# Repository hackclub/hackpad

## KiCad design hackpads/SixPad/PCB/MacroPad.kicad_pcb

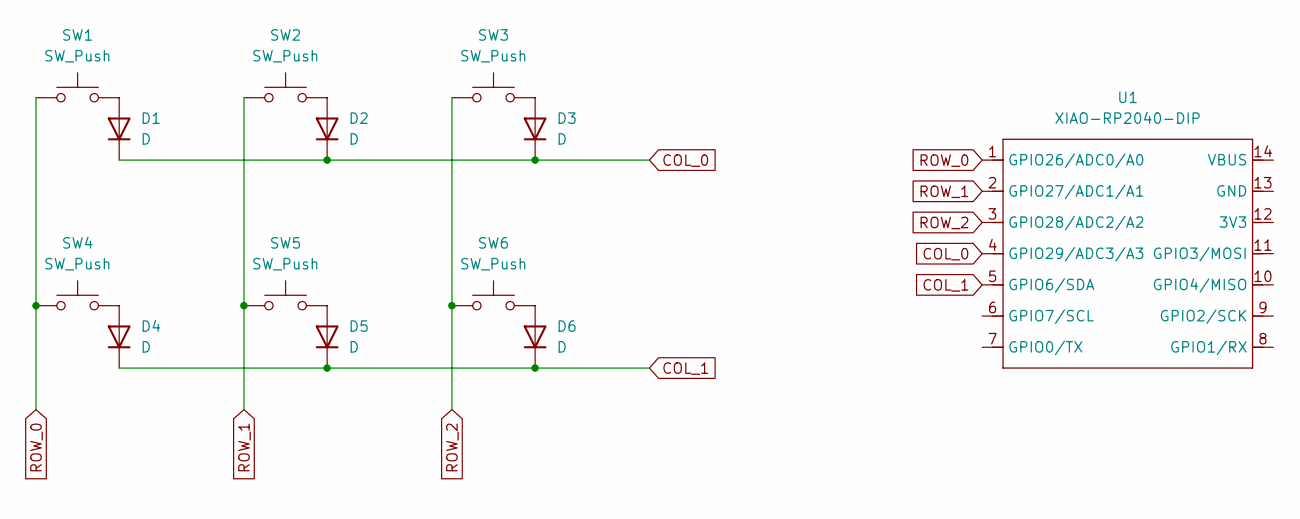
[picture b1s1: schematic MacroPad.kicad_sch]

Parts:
D1, D2, D3, D4, D5, D6: D; D_DO-35_SOD27_P7.62mm_Horizontal
SW1, SW2, SW3, SW4, SW5, SW6: SW_Push; SW_Cherry_MX_1.00u_PCB
U1: XIAO-RP2040-DIP

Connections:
COL_0: D1.1 (K), D2.1 (K), D3.1 (K), U1.4 (GPIO29/ADC3/A3)
COL_1: D4.1 (K), D5.1 (K), D6.1 (K), U1.5 (GPIO6/SDA)
unnamed: D1.2 (A), SW1.2
unnamed: D2.2 (A), SW2.2
unnamed: D3.2 (A), SW3.2
unnamed: D4.2 (A), SW4.2
unnamed: D5.2 (A), SW5.2
unnamed: D6.2 (A), SW6.2
ROW_0: SW1.1, SW4.1, U1.1 (GPIO26/ADC0/A0)
ROW_1: SW2.1, SW5.1, U1.2 (GPIO27/ADC1/A1)
ROW_2: SW3.1, SW6.1, U1.3 (GPIO28/ADC2/A2)

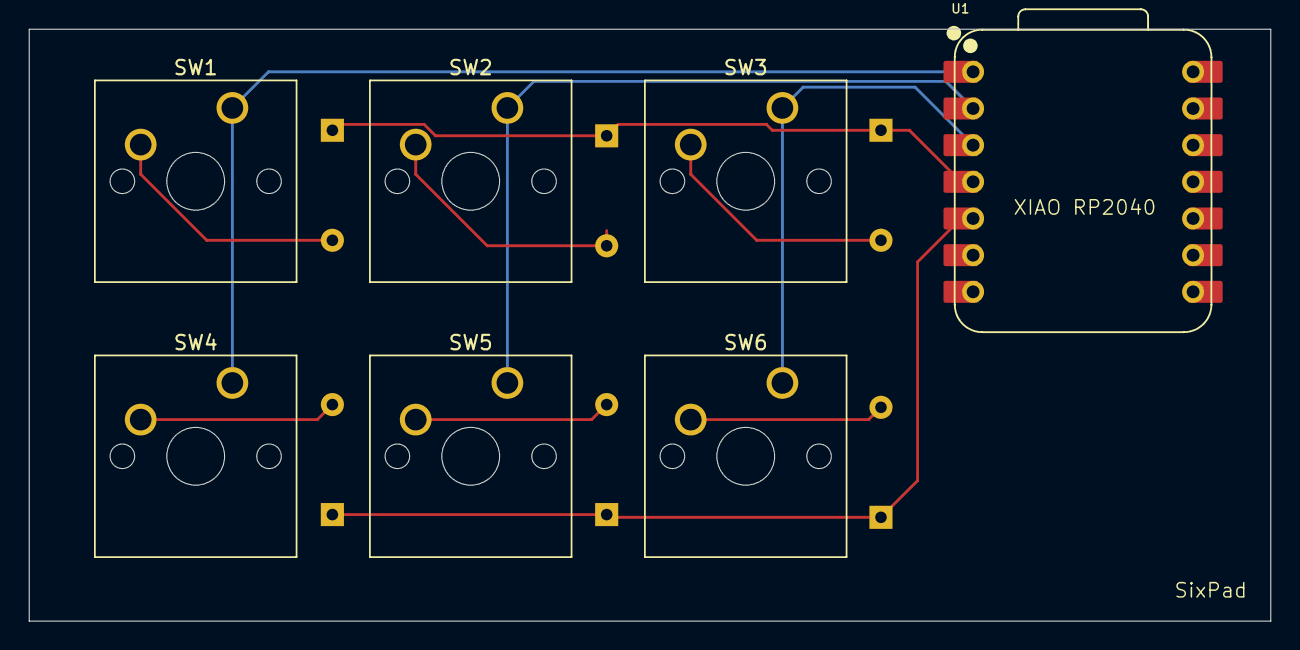
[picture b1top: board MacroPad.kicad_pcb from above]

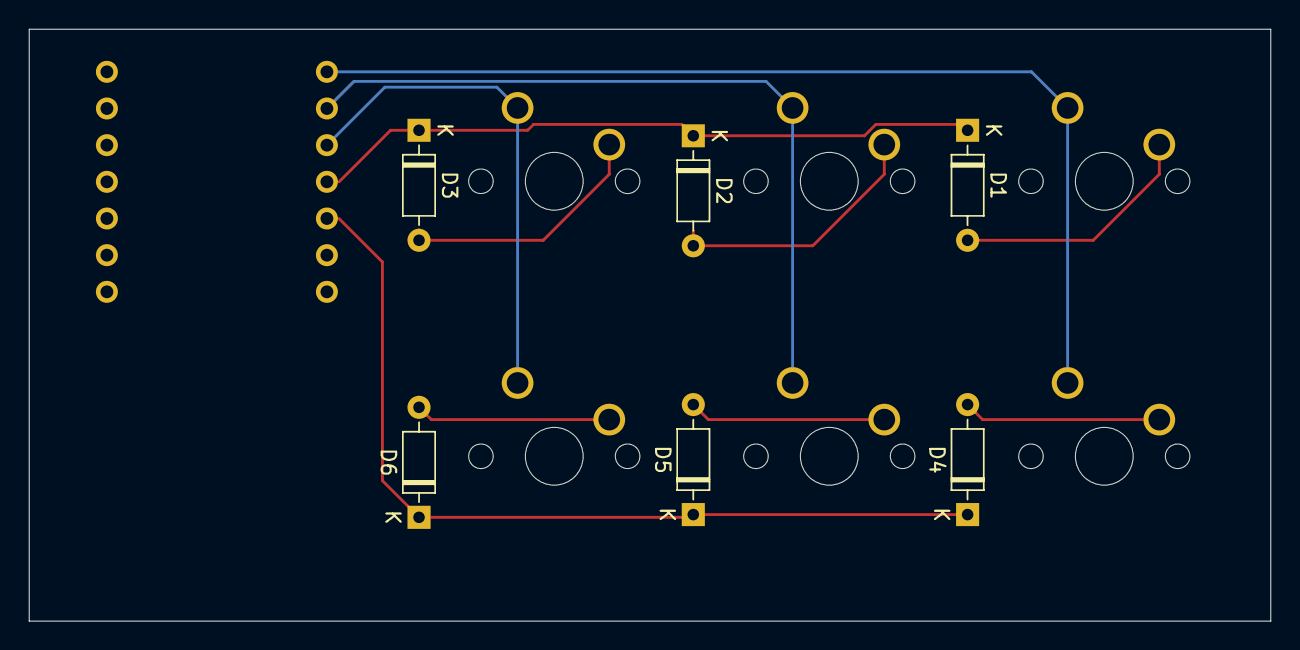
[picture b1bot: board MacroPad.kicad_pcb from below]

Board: 2 copper layers, 86.0 x 41.0 mm, 13 parts (6 on the bottom side), 11 nets.

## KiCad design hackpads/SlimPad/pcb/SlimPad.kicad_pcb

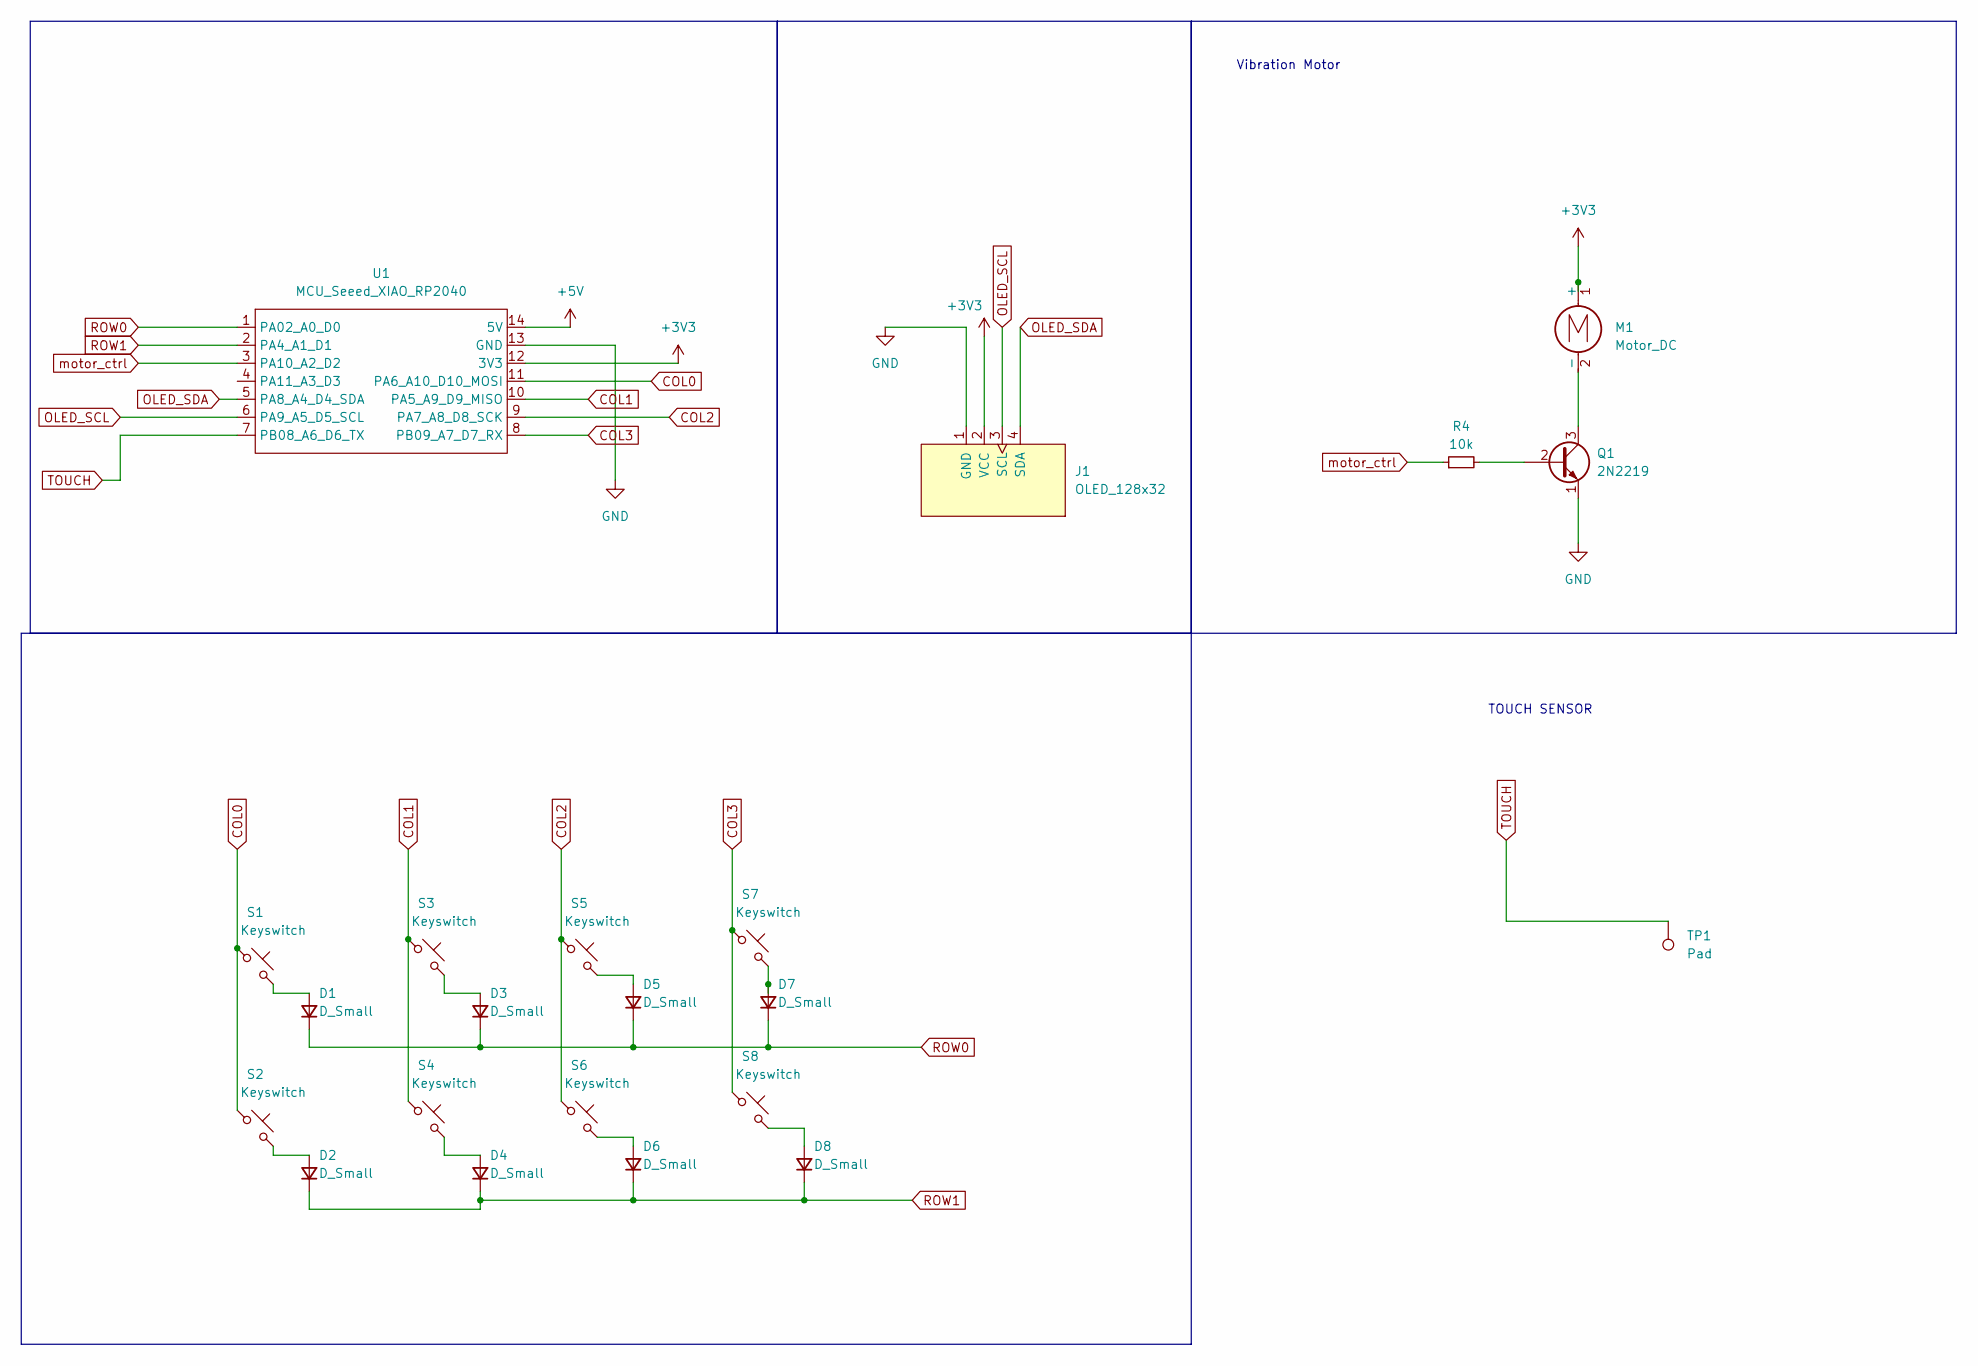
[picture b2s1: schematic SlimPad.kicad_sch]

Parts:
D1, D2, D3, D4, D5, D6, D7, D8: D_Small; Diode_DO-35
J1: OLED_128x32
M1: Motor_DC; PinHeader_2x01_P2.54mm_Vertical_SMD
Q1: 2N2219; TO-92L
R4: 10k; R_Axial_DIN0207_L6.3mm_D2.5mm_P7.62mm_Horizontal
S1, S2, S3, S4, S5, S6, S7, S8: Keyswitch; Hotswap_Choc_V1V2_1.00u
TP1: Pad; TestPoint_Pad_4.0x4.0mm
U1: MCU_Seeed_XIAO_RP2040; Seeed_XIAO_RP2040

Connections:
+3V3: J1.2 (VCC), M1.1 (+), U1.12 (3V3)
+5V: U1.14 (5V)
COL0: S1.1, S2.1, U1.11 (PA6_A10_D10_MOSI)
COL1: S3.1, S4.1, U1.10 (PA5_A9_D9_MISO)
COL2: S5.1, S6.1, U1.9 (PA7_A8_D8_SCK)
COL3: S7.1, S8.1, U1.8 (PB09_A7_D7_RX)
GND: J1.1 (GND), Q1.1 (E), U1.13 (GND)
unnamed: D1.2 (A), S1.2
unnamed: D2.2 (A), S2.2
unnamed: D3.2 (A), S3.2
unnamed: D4.2 (A), S4.2
unnamed: D5.2 (A), S5.2
unnamed: D6.2 (A), S6.2
unnamed: D7.2 (A), S7.2
unnamed: D8.2 (A), S8.2
unnamed: M1.2 (-), Q1.3 (C)
unnamed: Q1.2 (B), R4.2
OLED_SCL: J1.3 (SCL), U1.6 (PA9_A5_D5_SCL)
OLED_SDA: J1.4 (SDA), U1.5 (PA8_A4_D4_SDA)
ROW0: D1.1 (K), D3.1 (K), D5.1 (K), D7.1 (K), U1.1 (PA02_A0_D0)
ROW1: D2.1 (K), D4.1 (K), D6.1 (K), D8.1 (K), U1.2 (PA4_A1_D1)
TOUCH: TP1.1, U1.7 (PB08_A6_D6_TX)
motor_ctrl: R4.1, U1.3 (PA10_A2_D2)

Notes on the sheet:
Vibration Motor
TOUCH SENSOR

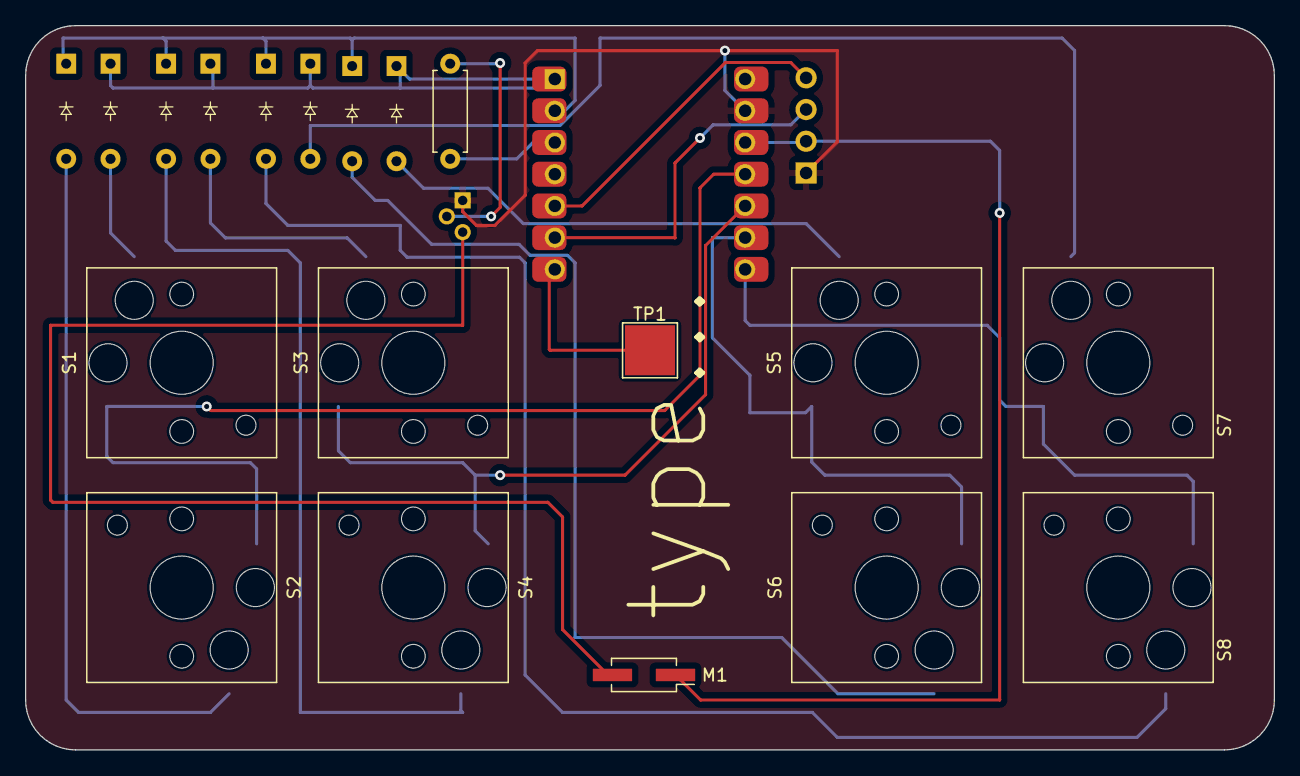
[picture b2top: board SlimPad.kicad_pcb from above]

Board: 2 copper layers, 100.0 x 58.0 mm, 22 parts (1 on the bottom side), 22 nets.

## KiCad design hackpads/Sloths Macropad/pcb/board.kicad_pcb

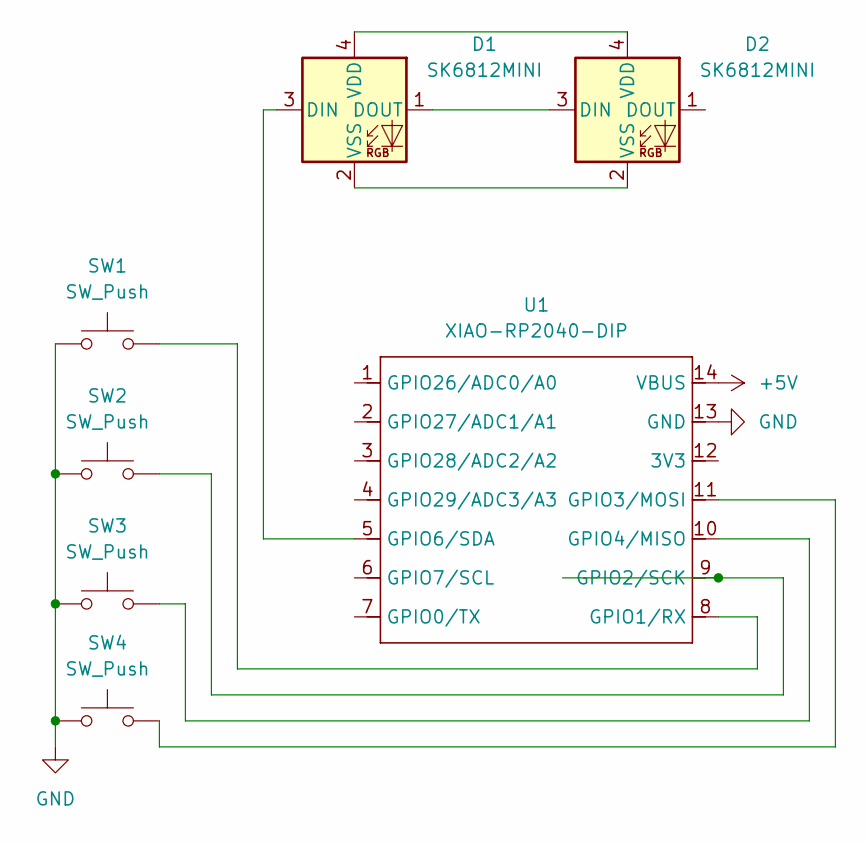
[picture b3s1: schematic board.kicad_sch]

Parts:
D1, D2: SK6812MINI; LED_SK6812MINI_PLCC4_3.5x3.5mm_P1.75mm
SW1, SW2, SW3, SW4: SW_Push; SW_Cherry_MX_1.00u_PCB
U1: XIAO-RP2040-DIP

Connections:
+5V: U1.14 (VBUS)
GND: SW1.1, SW2.1, SW3.1, SW4.1, U1.13 (GND)
unnamed: D1.3 (DIN), U1.5 (GPIO6/SDA)
unnamed: D1.1 (DOUT), D2.3 (DIN)
unnamed: D1.4 (VDD), D2.4 (VDD)
unnamed: D1.2 (VSS), D2.2 (VSS)
unnamed: SW1.2, U1.8 (GPIO1/RX)
unnamed: SW2.2, U1.9 (GPIO2/SCK)
unnamed: SW4.2, U1.11 (GPIO3/MOSI)
unnamed: SW3.2, U1.10 (GPIO4/MISO)

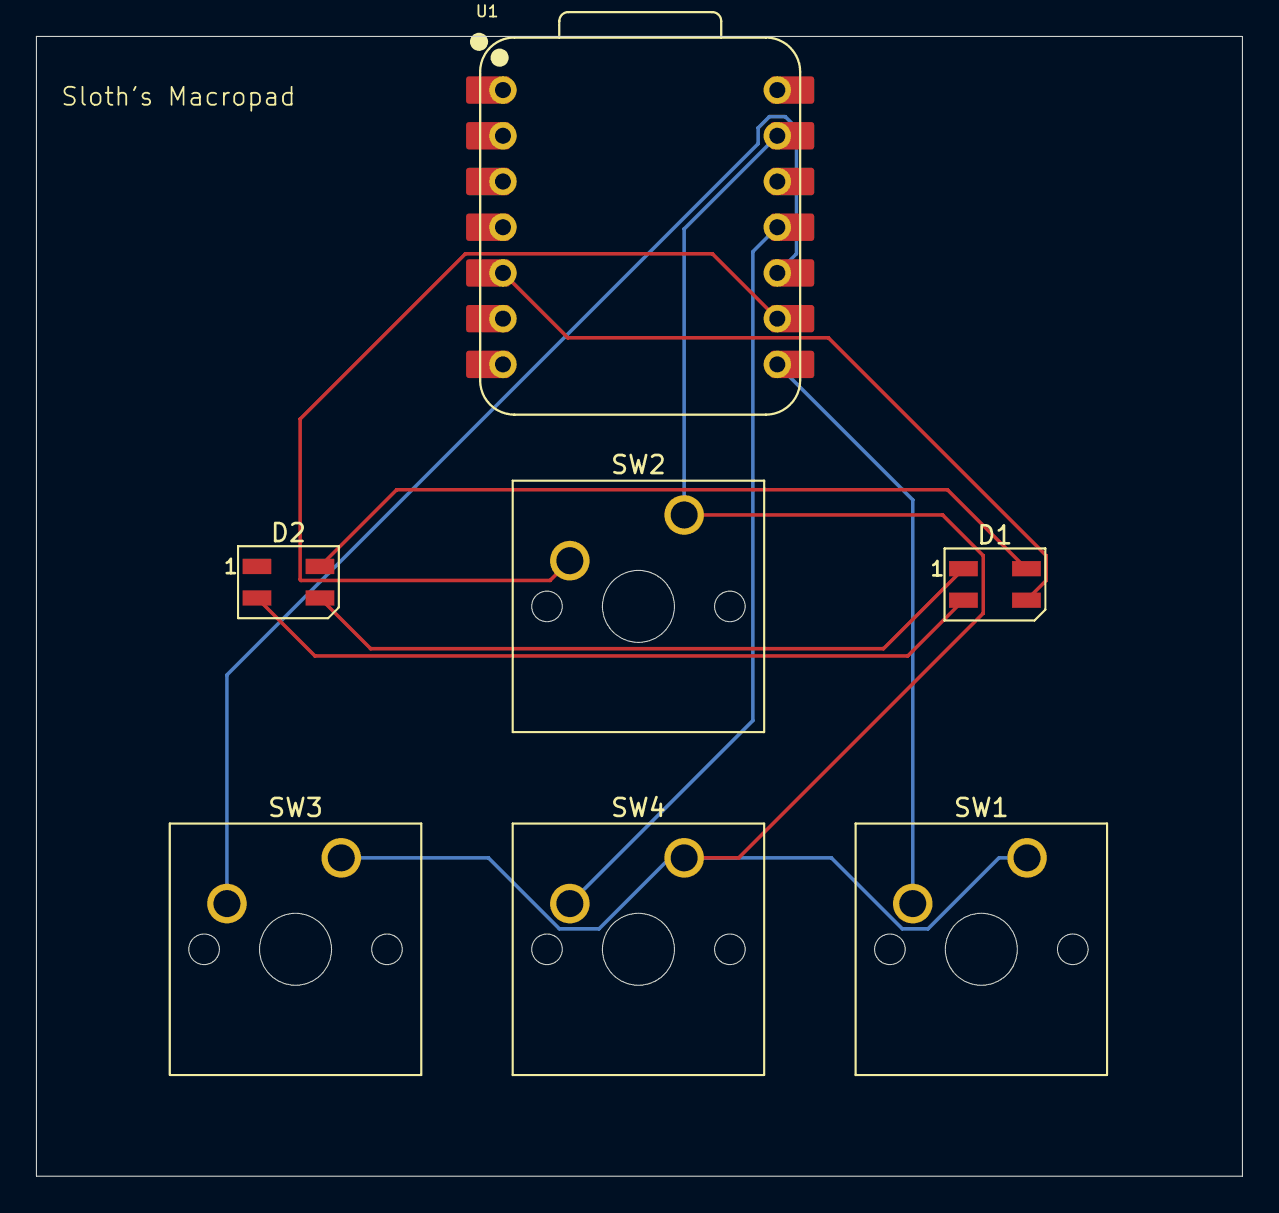
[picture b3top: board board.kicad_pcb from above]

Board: 2 copper layers, 67.0 x 63.3 mm, 7 parts (0 on the bottom side), 9 nets.

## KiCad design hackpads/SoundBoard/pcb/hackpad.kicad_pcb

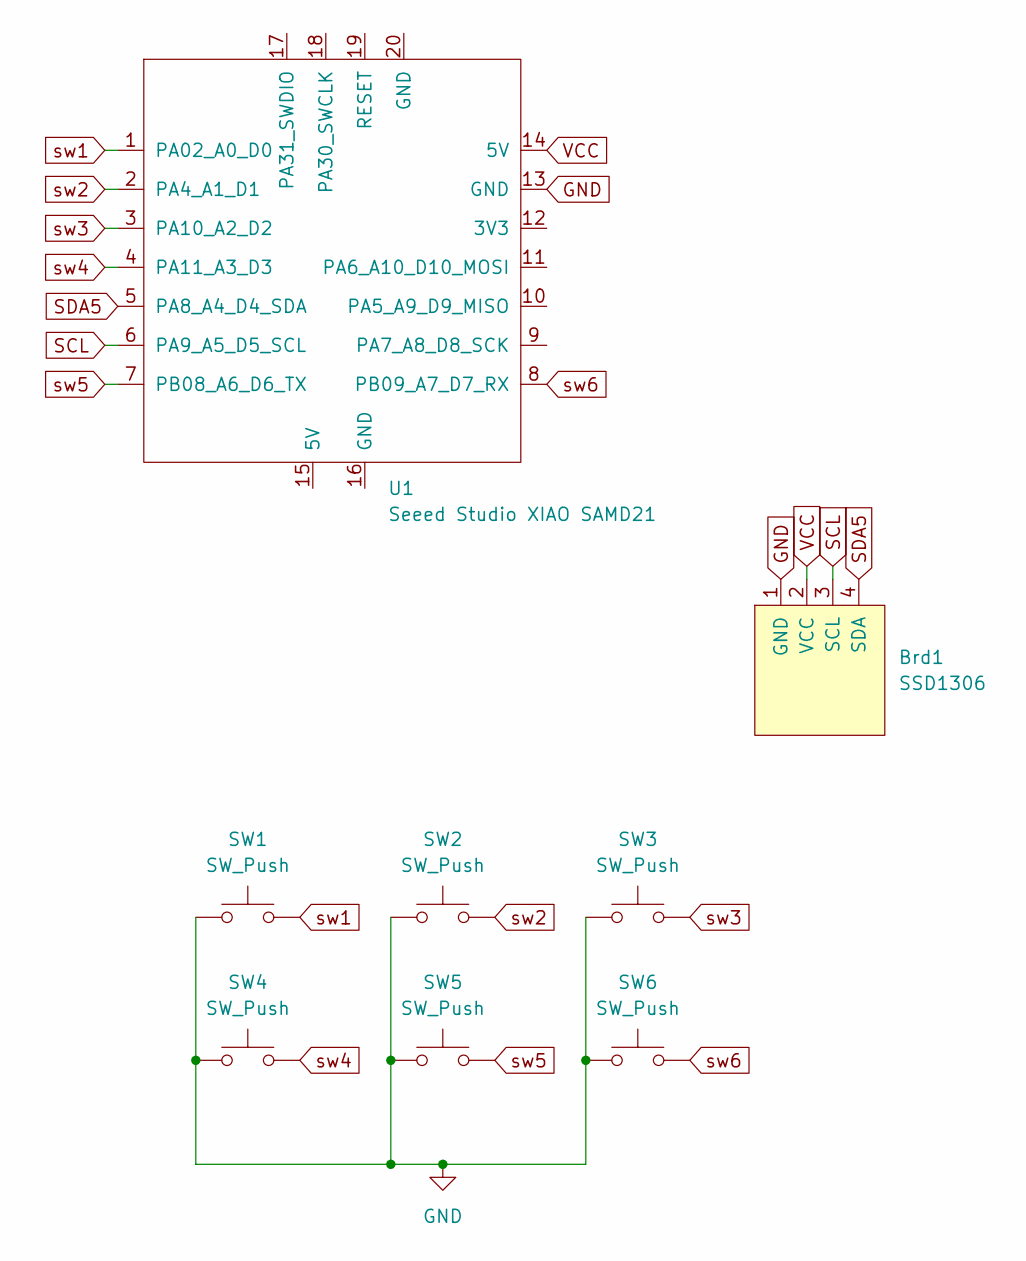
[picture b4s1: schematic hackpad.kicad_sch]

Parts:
Brd1: SSD1306; 128x64OLED
SW1: SW_Push; SW_Cherry_MX_1.00u_PCB
SW2: SW_Push; SW_Cherry_MX_1.00u_Plate
SW3: SW_Push; SW_Cherry_MX_1.25u_PCB
SW4: SW_Push; SW_Cherry_MX_1.25u_Plate
SW5: SW_Push; SW_Cherry_MX_1.50u_PCB
SW6: SW_Push; SW_Cherry_MX_1.50u_Plate
U1: Seeed Studio XIAO SAMD21; XIAO-Generic-Thruhole-14P-2.54-21X17.8MM

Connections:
GND: Brd1.1 (GND), SW1.1, SW2.1, SW3.1, SW4.1, SW5.1, SW6.1, U1.13 (GND)
SCL: Brd1.3 (SCL), U1.6 (PA9_A5_D5_SCL)
SDA5: Brd1.4 (SDA), U1.5 (PA8_A4_D4_SDA)
VCC: Brd1.2 (VCC), U1.14 (5V)
sw1: SW1.2, U1.1 (PA02_A0_D0)
sw2: SW2.2, U1.2 (PA4_A1_D1)
sw3: SW3.2, U1.3 (PA10_A2_D2)
sw4: SW4.2, U1.4 (PA11_A3_D3)
sw5: SW5.2, U1.7 (PB08_A6_D6_TX)
sw6: SW6.2, U1.8 (PB09_A7_D7_RX)

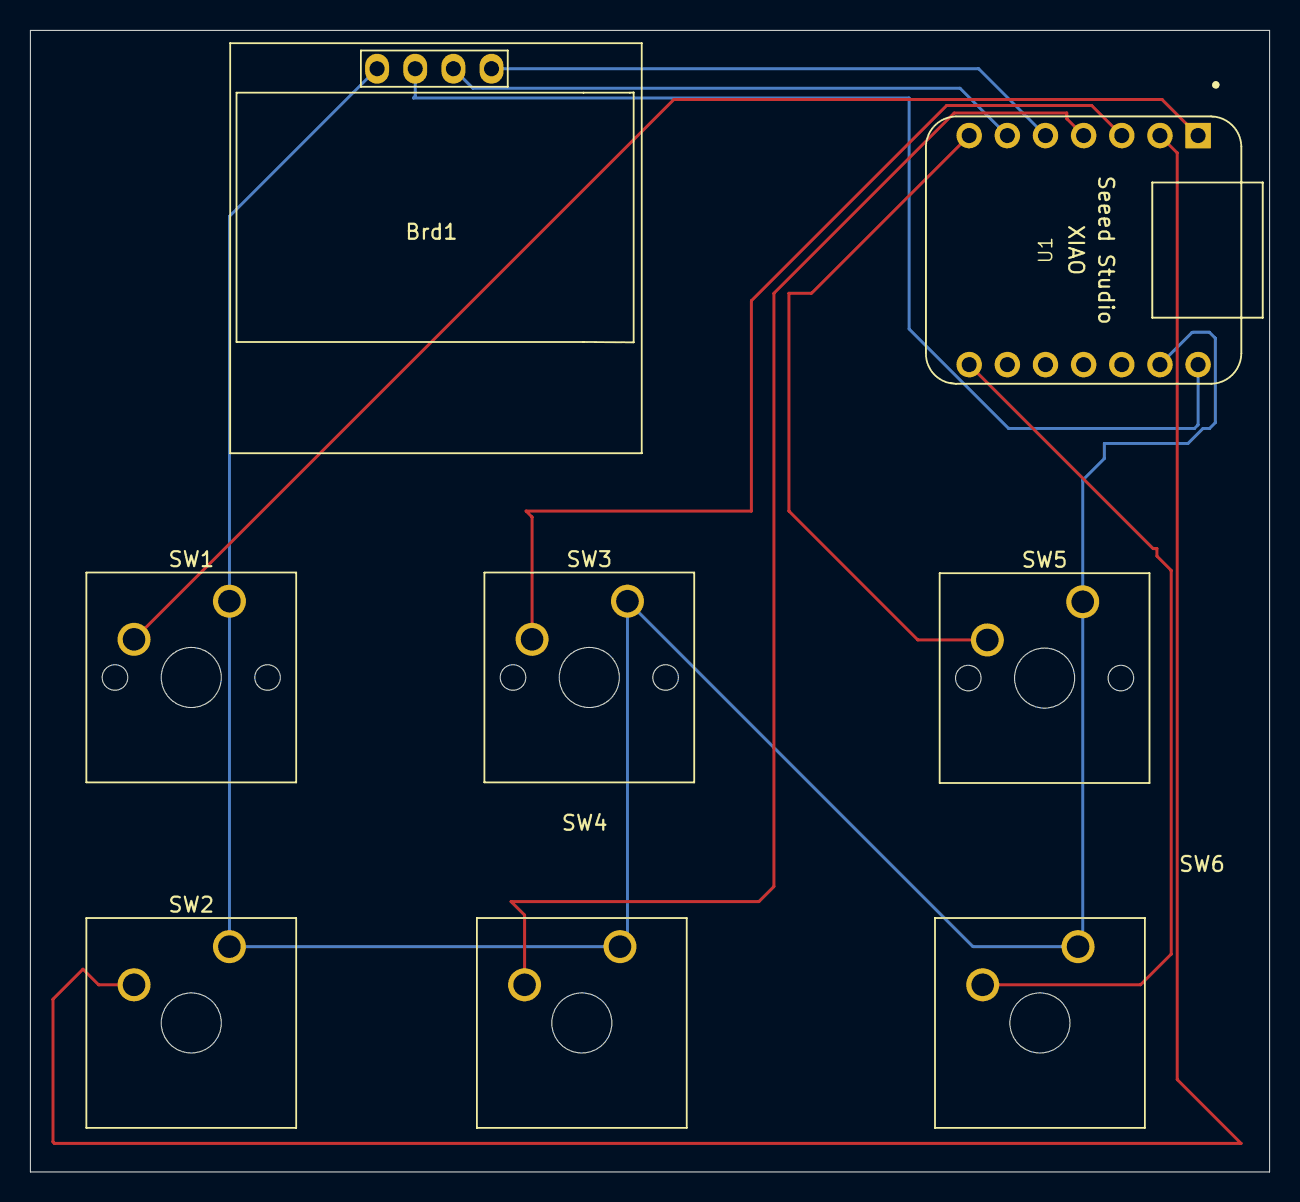
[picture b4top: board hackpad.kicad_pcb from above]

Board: 2 copper layers, 82.5 x 76.0 mm, 8 parts (0 on the bottom side), 10 nets.

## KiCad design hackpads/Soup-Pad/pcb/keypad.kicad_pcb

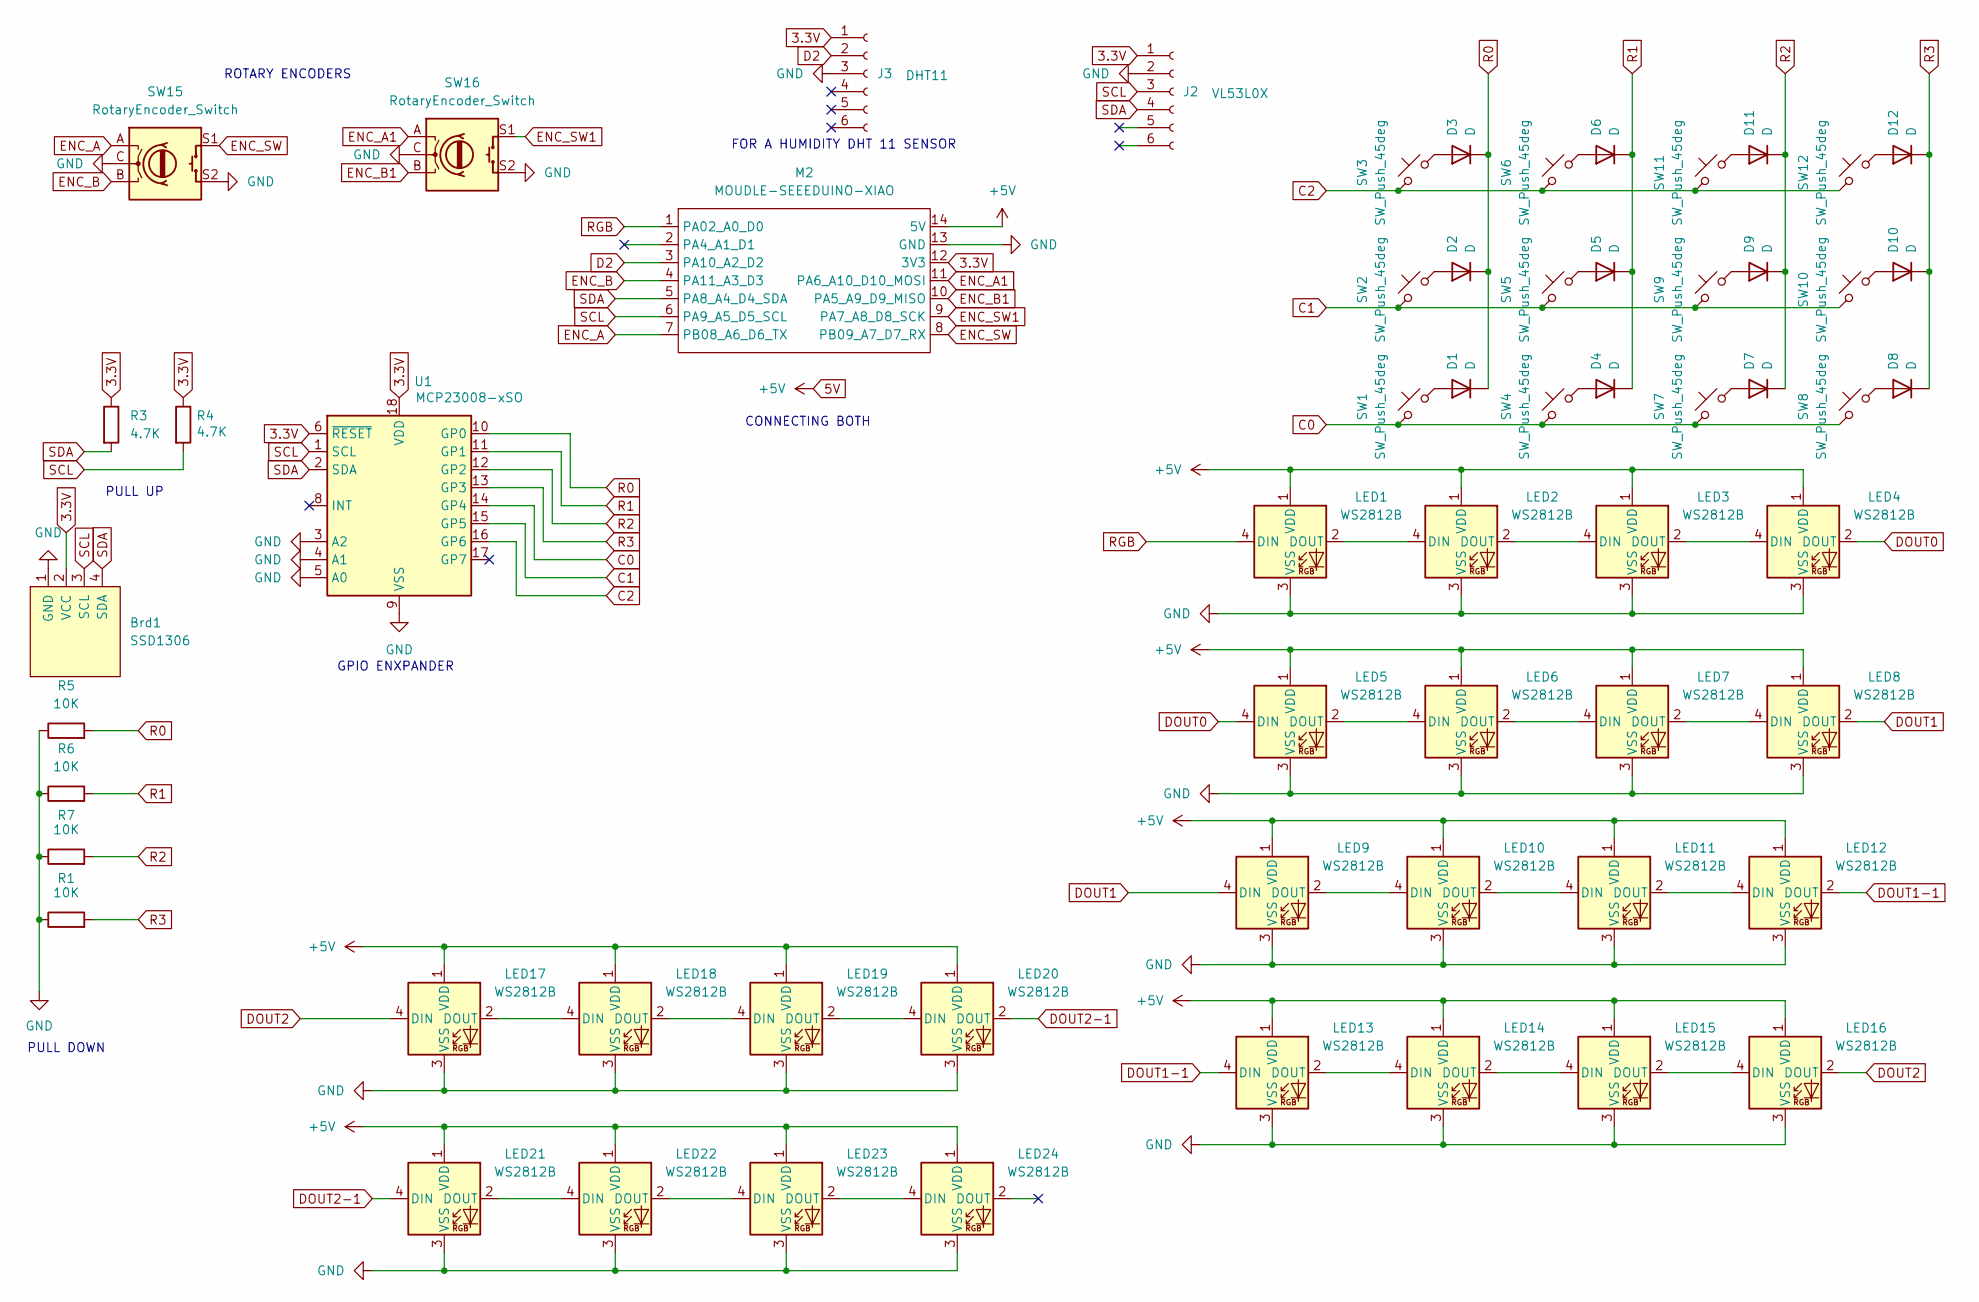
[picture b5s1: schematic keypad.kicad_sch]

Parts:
Brd1: SSD1306; SSD1306_0.96_Oled
D1, D2, D3, D4, D5, D6, D7, D8, D9, D10, D11, D12: D; D_DO-35_SOD27_P7.62mm_Horizontal
J2: VL53L0X; PinHeader_1x06_P2.54mm_Vertical
J3: DHT11; PinHeader_1x06_P2.54mm_Vertical
LED1, LED2, LED3, LED4, LED5, LED6, LED7, LED8, LED9, LED10, LED11, LED12, LED13, LED14, LED15, LED16, LED17, LED18, LED19, LED20, LED21, LED22, LED23, LED24: WS2812B; LED_WS2812B_PLCC4_5.0x5.0mm_P3.2mm
M2: MOUDLE-SEEEDUINO-XIAO; RP2040
R1, R5, R6, R7: 10K; R_0805_2012Metric_Pad1.20x1.40mm_HandSolder
R3, R4: 4.7K; R_0805_2012Metric_Pad1.20x1.40mm_HandSolder
SW1, SW2, SW3, SW4, SW5, SW6, SW7, SW8, SW9, SW10, SW11, SW12: SW_Push_45deg; SW_Cherry_MX_1.00u_PCB
SW15, SW16: RotaryEncoder_Switch; RotaryEncoder_Alps_EC11E-Switch_Vertical_H20mm
U1: MCP23008-xSO; SOIC-18W_7.5x11.6mm_P1.27mm

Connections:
3.3V: Brd1.2 (VCC), J2.1, J3.1, M2.12 (3V3), R3.1, R4.1, U1.6 (~RESET), U1.18 (VDD)
5V: LED1.1 (VDD), LED2.1 (VDD), LED3.1 (VDD), LED4.1 (VDD), LED5.1 (VDD), LED6.1 (VDD), LED7.1 (VDD), LED8.1 (VDD), LED9.1 (VDD), LED10.1 (VDD), LED11.1 (VDD), LED12.1 (VDD), LED13.1 (VDD), LED14.1 (VDD), LED15.1 (VDD), LED16.1 (VDD), LED17.1 (VDD), LED18.1 (VDD), LED19.1 (VDD), LED20.1 (VDD), LED21.1 (VDD), LED22.1 (VDD), LED23.1 (VDD), LED24.1 (VDD), M2.14 (5V)
C0: SW1.1, SW4.1, SW7.1, SW8.1, U1.14 (GP4)
C1: SW2.1, SW5.1, SW9.1, SW10.1, U1.15 (GP5)
C2: SW3.1, SW6.1, SW11.1, SW12.1, U1.16 (GP6)
D2: J3.2, M2.3 (PA10_A2_D2)
DOUT0: LED4.2 (DOUT), LED5.4 (DIN)
DOUT1: LED8.2 (DOUT), LED9.4 (DIN)
DOUT1-1: LED12.2 (DOUT), LED13.4 (DIN)
DOUT2: LED16.2 (DOUT), LED17.4 (DIN)
DOUT2-1: LED20.2 (DOUT), LED21.4 (DIN)
ENC_A: M2.7 (PB08_A6_D6_TX), SW15.A
ENC_A1: M2.11 (PA6_A10_D10_MOSI), SW16.A
ENC_B: M2.4 (PA11_A3_D3), SW15.B
ENC_B1: M2.10 (PA5_A9_D9_MISO), SW16.B
ENC_SW: M2.8 (PB09_A7_D7_RX), SW15.S1
ENC_SW1: M2.9 (PA7_A8_D8_SCK), SW16.S1
GND: Brd1.1 (GND), J2.2, J3.3, LED1.3 (VSS), LED2.3 (VSS), LED3.3 (VSS), LED4.3 (VSS), LED5.3 (VSS), LED6.3 (VSS), LED7.3 (VSS), LED8.3 (VSS), LED9.3 (VSS), LED10.3 (VSS), LED11.3 (VSS), LED12.3 (VSS), LED13.3 (VSS), LED14.3 (VSS), LED15.3 (VSS), LED16.3 (VSS), LED17.3 (VSS), LED18.3 (VSS), LED19.3 (VSS), LED20.3 (VSS), LED21.3 (VSS), LED22.3 (VSS), LED23.3 (VSS), LED24.3 (VSS), M2.13 (GND), R1.1, R5.1, R6.1, R7.1, SW15.C, SW15.S2, SW16.C, SW16.S2, U1.3 (A2), U1.4 (A1), U1.5 (A0), U1.9 (VSS)
unnamed: D1.2 (A), SW1.2
unnamed: D2.2 (A), SW2.2
unnamed: D3.2 (A), SW3.2
unnamed: D4.2 (A), SW4.2
unnamed: D5.2 (A), SW5.2
unnamed: D6.2 (A), SW6.2
unnamed: D7.2 (A), SW7.2
unnamed: D8.2 (A), SW8.2
unnamed: D9.2 (A), SW9.2
unnamed: D10.2 (A), SW10.2
unnamed: D11.2 (A), SW11.2
unnamed: D12.2 (A), SW12.2
unnamed: LED1.2 (DOUT), LED2.4 (DIN)
unnamed: LED2.2 (DOUT), LED3.4 (DIN)
unnamed: LED3.2 (DOUT), LED4.4 (DIN)
unnamed: LED5.2 (DOUT), LED6.4 (DIN)
unnamed: LED6.2 (DOUT), LED7.4 (DIN)
unnamed: LED7.2 (DOUT), LED8.4 (DIN)
unnamed: LED9.2 (DOUT), LED10.4 (DIN)
unnamed: LED10.2 (DOUT), LED11.4 (DIN)
unnamed: LED11.2 (DOUT), LED12.4 (DIN)
unnamed: LED13.2 (DOUT), LED14.4 (DIN)
unnamed: LED14.2 (DOUT), LED15.4 (DIN)
unnamed: LED15.2 (DOUT), LED16.4 (DIN)
unnamed: LED17.2 (DOUT), LED18.4 (DIN)
unnamed: LED18.2 (DOUT), LED19.4 (DIN)
unnamed: LED19.2 (DOUT), LED20.4 (DIN)
unnamed: LED21.2 (DOUT), LED22.4 (DIN)
unnamed: LED22.2 (DOUT), LED23.4 (DIN)
unnamed: LED23.2 (DOUT), LED24.4 (DIN)
R0: D1.1 (K), D2.1 (K), D3.1 (K), R5.2, U1.10 (GP0)
R1: D4.1 (K), D5.1 (K), D6.1 (K), R6.2, U1.11 (GP1)
R2: D7.1 (K), D9.1 (K), D11.1 (K), R7.2, U1.12 (GP2)
R3: D8.1 (K), D10.1 (K), D12.1 (K), R1.2, U1.13 (GP3)
RGB: LED1.4 (DIN), M2.1 (PA02_A0_D0)
SCL: Brd1.3 (SCL), J2.3, M2.6 (PA9_A5_D5_SCL), R4.2, U1.1 (SCL)
SDA: Brd1.4 (SDA), J2.4, M2.5 (PA8_A4_D4_SDA), R3.2, U1.2 (SDA)

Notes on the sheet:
GPIO ENXPANDER
PULL UP
CONNECTING BOTH
ROTARY ENCODERS
FOR A HUMIDITY DHT 11 SENSOR
PULL DOWN

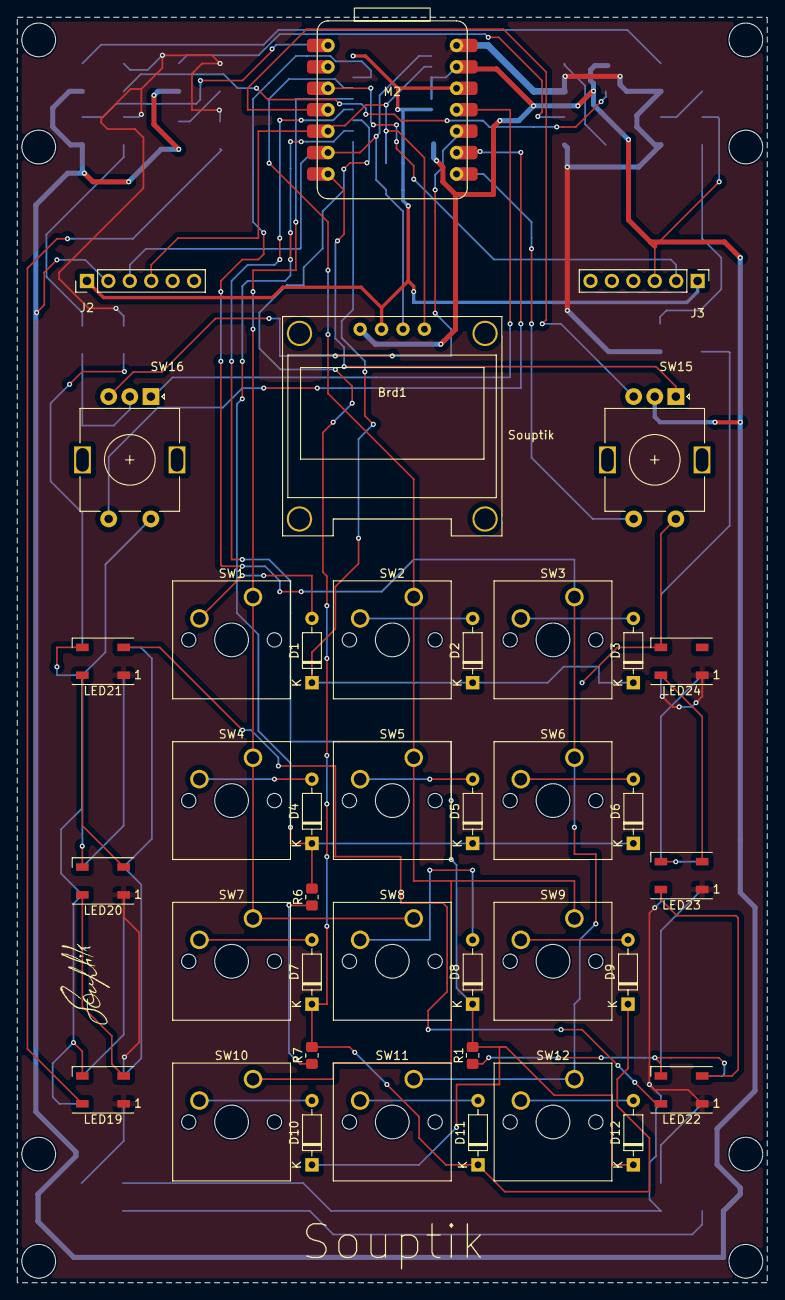
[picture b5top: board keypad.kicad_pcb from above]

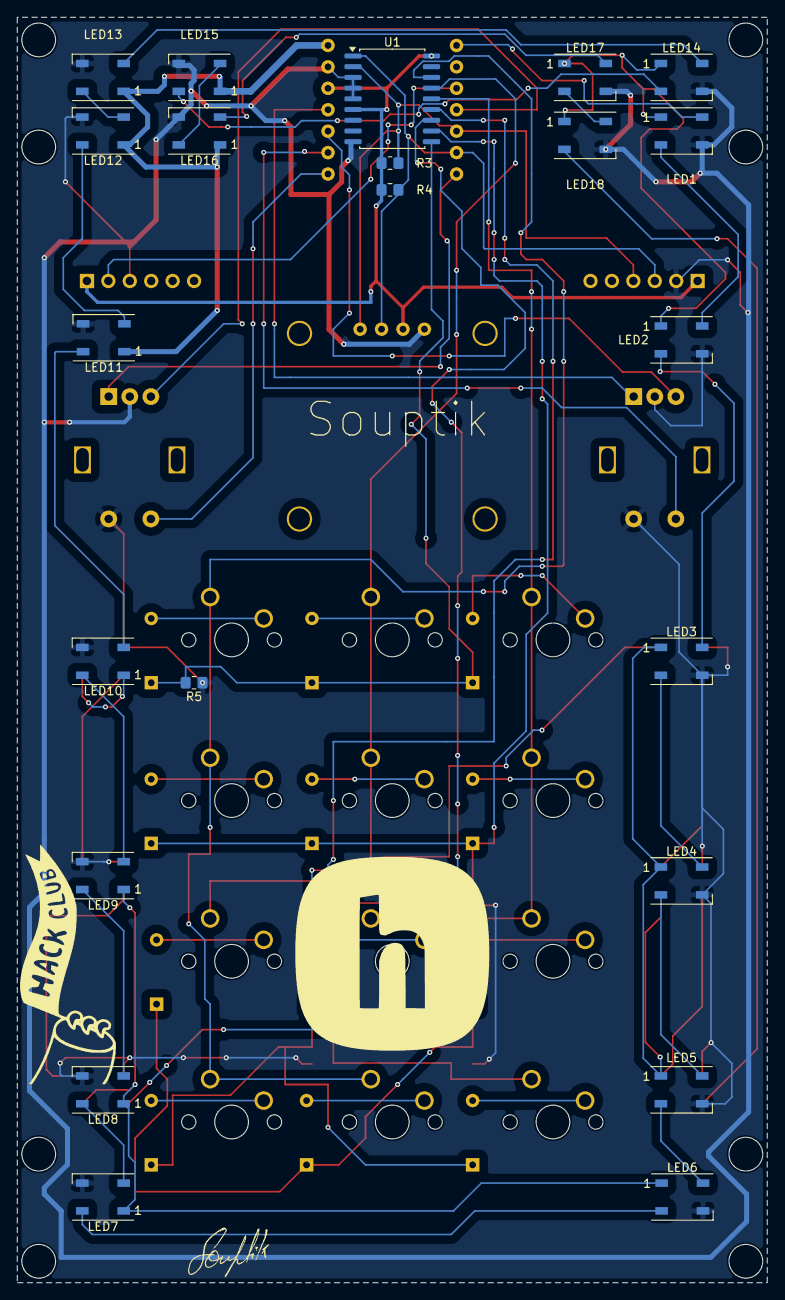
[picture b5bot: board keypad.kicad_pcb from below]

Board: 2 copper layers, 88.9 x 150.0 mm, 61 parts (22 on the bottom side), 55 nets.
